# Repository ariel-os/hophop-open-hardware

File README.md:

hophop: Open Hardware
=====================

This repository will contains the design files
for hardware developed for hophop.

Items
-----

* [Grasshopper Nymph](./grasshopper-nymph/README.md)

  Status: Boards built and are being tested.

Branding
--------

These boards are developed as part of the Ariel OS project (as is the hophop stack),
will run Ariel OS based software from the start,
and may come with the Ariel OS logo.

License
-------

Data in this repository is licensed under the terms of [CERN-OHL-P-2.0](https://ohwr.org/cern_ohl_p_v2.pdf),
unless specified differently (when derived from third party content).

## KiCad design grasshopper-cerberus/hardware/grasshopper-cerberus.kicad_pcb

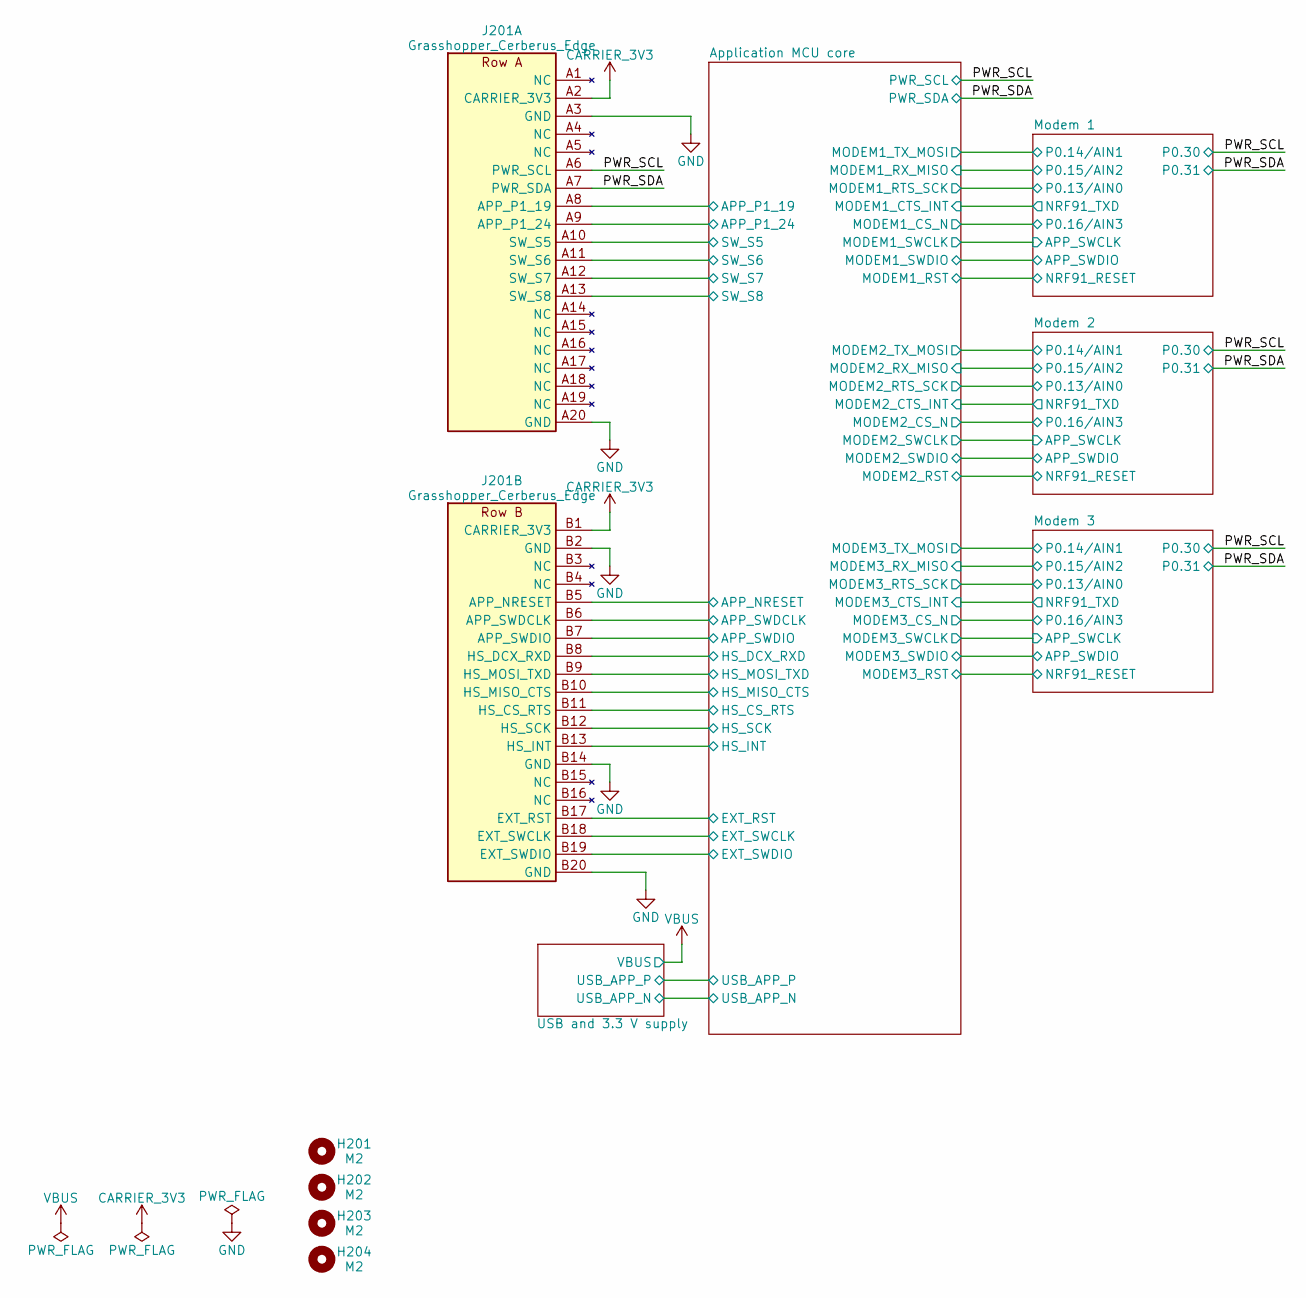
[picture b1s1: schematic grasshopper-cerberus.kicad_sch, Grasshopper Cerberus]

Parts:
H201, H202, H203, H204: M2; MountingHole_2.2mm_M2
J201: Grasshopper_Cerberus_Edge; Grasshopper_Cerberus_Edge_2x20_P2.54mm_Castellated_Row45.72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

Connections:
/Application MCU core/APP_NRESET: J201.B5 (APP_NRESET); also elsewhere on the board
/Application MCU core/APP_P1_19: J201.A8 (APP_P1_19); also elsewhere on the board
/Application MCU core/APP_P1_24: J201.A9 (APP_P1_24); also elsewhere on the board
/Application MCU core/APP_SWDCLK: J201.B6 (APP_SWDCLK); also elsewhere on the board
/Application MCU core/APP_SWDIO: J201.B7 (APP_SWDIO); also elsewhere on the board
/Application MCU core/EXT_RST: J201.B17 (EXT_RST); also elsewhere on the board
/Application MCU core/EXT_SWCLK: J201.B18 (EXT_SWCLK); also elsewhere on the board
/Application MCU core/EXT_SWDIO: J201.B19 (EXT_SWDIO); also elsewhere on the board
/Application MCU core/HS_CS_RTS: J201.B11 (HS_CS_RTS); also elsewhere on the board
/Application MCU core/HS_DCX_RXD: J201.B8 (HS_DCX_RXD); also elsewhere on the board
/Application MCU core/HS_INT: J201.B13 (HS_INT); also elsewhere on the board
/Application MCU core/HS_MISO_CTS: J201.B10 (HS_MISO_CTS); also elsewhere on the board
/Application MCU core/HS_MOSI_TXD: J201.B9 (HS_MOSI_TXD); also elsewhere on the board
/Application MCU core/HS_SCK: J201.B12 (HS_SCK); also elsewhere on the board
/Application MCU core/SW_S5: J201.A10 (SW_S5); also elsewhere on the board
/Application MCU core/SW_S6: J201.A11 (SW_S6); also elsewhere on the board
/Application MCU core/SW_S7: J201.A12 (SW_S7); also elsewhere on the board
/Application MCU core/SW_S8: J201.A13 (SW_S8); also elsewhere on the board
/PWR_SCL: J201.A6 (PWR_SCL); also elsewhere on the board
/PWR_SDA: J201.A7 (PWR_SDA); also elsewhere on the board
CARRIER_3V3: J201.A2 (CARRIER_3V3), J201.B1 (CARRIER_3V3); also elsewhere on the board
GND: J201.A3 (GND), J201.A20 (GND), J201.B2 (GND), J201.B14 (GND), J201.B20 (GND); also elsewhere on the board

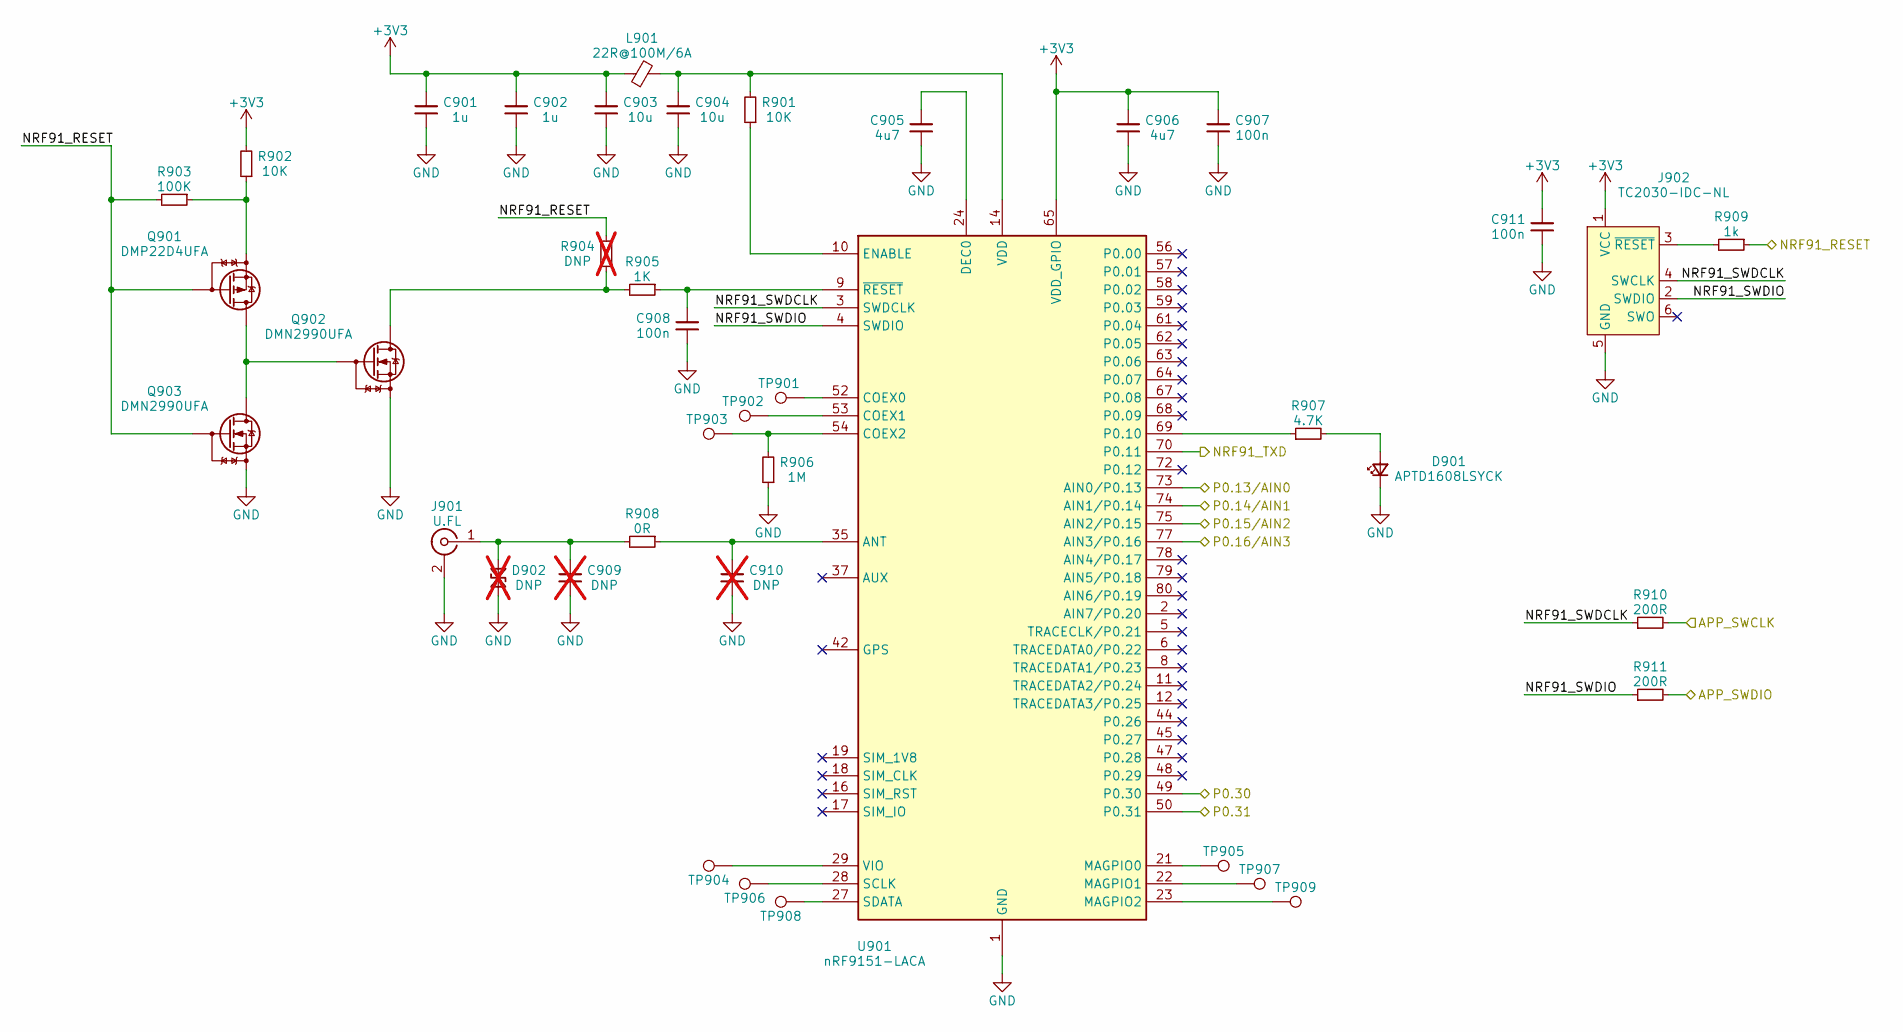
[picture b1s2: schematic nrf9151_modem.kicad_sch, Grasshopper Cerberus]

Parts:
C901, C902: 1u; C_0402_1005Metric; MPN GRM155R61A105KE15D
C903, C904: 10u; C_0603_1608Metric; MPN GRM188R61A106KE69D
C905, C906: 4u7; C_0402_1005Metric; MPN GRM155R61A475MEAAD
C907, C908: 100n; C_0402_1005Metric; MPN GRM155R71C104KA88D
C909, C910: DNP; C_0402_1005Metric; not fitted
C911: 100n; C_0402_1005Metric
D901: APTD1608LSYCK; LED_0603_1608Metric; MPN APTD1608LSYCK
D902: DNP; D_SOD-882; not fitted
J901: U.FL; U.FL_Hirose_U.FL-R-SMT-1_Vertical; MPN U.FL-R-SMT-1(10)
J902: TC2030-IDC-NL; Tag-Connect_TC2030-IDC-NL_2x03_P1.27mm_Vertical
L901: 22R@100M/6A; L_0805_2012Metric; MPN BLM21PG220SN1D
Q901: DMP22D4UFA; Diodes_X2-DFN0806-3_0.8x0.6mm_P0.35mm_GSD; MPN DMP22D4UFA-7B
Q902, Q903: DMN2990UFA; Diodes_X2-DFN0806-3_0.8x0.6mm_P0.35mm_GSD; MPN DMN2990UFA-7B
R901, R902: 10K; R_0402_1005Metric; MPN CRCW040210K0FKED
R903: 100K; R_0402_1005Metric; MPN CRCW0402100KFKED
R904: DNP; R_0402_1005Metric; MPN CRCW04020000Z0ED; not fitted
R905: 1K; R_0402_1005Metric; MPN CRCW04021K00FKED
R906: 1M; R_0402_1005Metric; MPN CRCW04021M00FKED
R907: 4.7K; R_0402_1005Metric; Tolerance 1%; MPN CRCW04024K70FKED
R908: 0R; R_0402_1005Metric; MPN CRCW04020000Z0ED
R909: 1k; R_0402_1005Metric
R910, R911: 200R; R_0402_1005Metric
TP901, TP902, TP903, TP904, TP905, TP906, TP907, TP908, TP909: TestPoint; TestPoint_Pad_D1.0mm_Compact
U901: nRF9151-LACA; Nordic_nRF9151-LAxx_LGA-80-33EP_12.1x11.1mm_P0.5mm; MPN nRF9151-LACA-R7

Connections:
+3V3: C901.2, C902.2, C903.2, C906.2, C907.2, C911.1, J902.1 (VCC), L901.1, R902.2, U901.65 (VDD_GPIO); also elsewhere on the board
/Application MCU core/MODEM1_CS_N: U901.77 (AIN3/P0.16); also elsewhere on the board
/Application MCU core/MODEM1_CTS_INT: U901.70 (P0.11); also elsewhere on the board
/Application MCU core/MODEM1_RTS_SCK: U901.73 (AIN0/P0.13); also elsewhere on the board
/Application MCU core/MODEM1_RX_MISO: U901.75 (AIN2/P0.15); also elsewhere on the board
/Application MCU core/MODEM1_SWCLK: R910.2; also elsewhere on the board
/Application MCU core/MODEM1_SWDIO: R911.2; also elsewhere on the board
/Application MCU core/MODEM1_TX_MOSI: U901.74 (AIN1/P0.14); also elsewhere on the board
/Modem 1/NRF91_RESET: Q901.G, Q903.G, R903.2, R904.1, R909.1; also elsewhere on the board
/Modem 1/NRF91_SWDCLK: J902.4 (SWCLK), R910.1, U901.3 (SWDCLK)
/Modem 1/NRF91_SWDIO: J902.2 (SWDIO), R911.1, U901.4 (SWDIO)
/PWR_SCL: U901.49 (P0.30); also elsewhere on the board
/PWR_SDA: U901.50 (P0.31); also elsewhere on the board
GND: C901.1, C902.1, C903.1, C904.1, C905.1, C906.1, C907.1, C908.1, C909.1, C910.1, C911.2, D901.1 (K), D902.2 (A2), J901.2 (Ext), J902.5 (GND), Q902.S, Q903.S, R906.1, U901.1 (GND), U901.7 (GND), U901.13 (GND), U901.15 (GND), U901.20 (GND), U901.25 (GND), U901.30 (GND), U901.34 (GND), U901.36 (GND), U901.38 (GND), U901.39 (GND), U901.40 (GND), U901.41 (GND), U901.43 (GND), U901.46 (GND), U901.51 (GND), U901.55 (GND), U901.60 (GND), U901.66 (GND), U901.71 (GND), U901.76 (GND), U901.105 (GND), U901.106 (GND), U901.107 (GND), U901.108 (GND), U901.109 (GND), U901.110 (GND), U901.111 (GND), U901.112 (GND), U901.113 (GND); also elsewhere on the board
unnamed: D901.2 (A), R907.2
unnamed: C909.2, D902.1 (A1), J901.1 (In), R908.2
unnamed: J902.3 (~RESET), R909.2
unnamed: Q901.D, Q902.G, Q903.D
unnamed: Q901.S, R902.1, R903.1
unnamed: Q902.D, R904.2, R905.2
unnamed: C910.2, R908.1, U901.35 (ANT)
unnamed: TP901.1 (1_1), U901.52 (COEX0)
unnamed: TP902.1 (1_1), U901.53 (COEX1)
unnamed: R906.2, TP903.1 (1_1), U901.54 (COEX2)
unnamed: C905.2, U901.24 (DEC0)
unnamed: R901.1, U901.10 (ENABLE)
unnamed: TP905.1 (1_1), U901.21 (MAGPIO0)
unnamed: TP907.1 (1_1), U901.22 (MAGPIO1)
unnamed: TP909.1 (1_1), U901.23 (MAGPIO2)
unnamed: R907.1, U901.69 (P0.10)
unnamed: TP906.1 (1_1), U901.28 (SCLK)
unnamed: TP908.1 (1_1), U901.27 (SDATA)
unnamed: C904.2, L901.2, R901.2, U901.14 (VDD)
unnamed: TP904.1 (1_1), U901.29 (VIO)
unnamed: C908.2, R905.1, U901.9 (~RESET)

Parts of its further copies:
C1001, C1002, C1101, C1102: 1u; C_0402_1005Metric; MPN GRM155R61A105KE15D
C1003, C1004, C1103, C1104: 10u; C_0603_1608Metric; MPN GRM188R61A106KE69D
C1005, C1006, C1105, C1106: 4u7; C_0402_1005Metric; MPN GRM155R61A475MEAAD
C1007, C1008, C1107, C1108: 100n; C_0402_1005Metric; MPN GRM155R71C104KA88D
C1009, C1010, C1109, C1110: DNP; C_0402_1005Metric; not fitted
C1011, C1111: 100n; C_0402_1005Metric
D1001, D1101: APTD1608LSYCK; LED_0603_1608Metric; MPN APTD1608LSYCK
D1002, D1102: DNP; D_SOD-882; not fitted
J1001, J1101: U.FL; U.FL_Hirose_U.FL-R-SMT-1_Vertical; MPN U.FL-R-SMT-1(10)
J1002, J1102: TC2030-IDC-NL; Tag-Connect_TC2030-IDC-NL_2x03_P1.27mm_Vertical
L1001, L1101: 22R@100M/6A; L_0805_2012Metric; MPN BLM21PG220SN1D
Q1001, Q1101: DMP22D4UFA; Diodes_X2-DFN0806-3_0.8x0.6mm_P0.35mm_GSD; MPN DMP22D4UFA-7B
Q1002, Q1003, Q1102, Q1103: DMN2990UFA; Diodes_X2-DFN0806-3_0.8x0.6mm_P0.35mm_GSD; MPN DMN2990UFA-7B
R1001, R1002, R1101, R1102: 10K; R_0402_1005Metric; MPN CRCW040210K0FKED
R1003, R1103: 100K; R_0402_1005Metric; MPN CRCW0402100KFKED
R1004, R1104: DNP; R_0402_1005Metric; MPN CRCW04020000Z0ED; not fitted
R1005, R1105: 1K; R_0402_1005Metric; MPN CRCW04021K00FKED
R1006, R1106: 1M; R_0402_1005Metric; MPN CRCW04021M00FKED
R1007, R1107: 4.7K; R_0402_1005Metric; Tolerance 1%; MPN CRCW04024K70FKED
R1008, R1108: 0R; R_0402_1005Metric; MPN CRCW04020000Z0ED
R1009, R1109: 1k; R_0402_1005Metric
R1010, R1011, R1110, R1111: 200R; R_0402_1005Metric
TP1001, TP1002, TP1003, TP1004, TP1005, TP1006, TP1007, TP1008, TP1009, TP1101, TP1102, TP1103, TP1104, TP1105, TP1106, TP1107, TP1108, TP1109: TestPoint; TestPoint_Pad_D1.0mm_Compact
U1001, U1101: nRF9151-LACA; Nordic_nRF9151-LAxx_LGA-80-33EP_12.1x11.1mm_P0.5mm; MPN nRF9151-LACA-R7

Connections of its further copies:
+3V3: C1001.2, C1002.2, C1003.2, C1006.2, C1007.2, C1011.1, C1101.2, C1102.2, C1103.2, C1106.2, C1107.2, C1111.1, J1002.1 (VCC), J1102.1 (VCC), L1001.1, L1101.1, R1002.2, R1102.2, U1001.65 (VDD_GPIO), U1101.65 (VDD_GPIO); also elsewhere on the board
/Application MCU core/MODEM2_CS_N: U1001.77 (AIN3/P0.16); also elsewhere on the board
/Application MCU core/MODEM2_CTS_INT: U1001.70 (P0.11); also elsewhere on the board
/Application MCU core/MODEM2_RTS_SCK: U1001.73 (AIN0/P0.13); also elsewhere on the board
/Application MCU core/MODEM2_RX_MISO: U1001.75 (AIN2/P0.15); also elsewhere on the board
/Application MCU core/MODEM2_SWCLK: R1010.2; also elsewhere on the board
/Application MCU core/MODEM2_SWDIO: R1011.2; also elsewhere on the board
/Application MCU core/MODEM2_TX_MOSI: U1001.74 (AIN1/P0.14); also elsewhere on the board
/Application MCU core/MODEM3_CS_N: U1101.77 (AIN3/P0.16); also elsewhere on the board
/Application MCU core/MODEM3_CTS_INT: U1101.70 (P0.11); also elsewhere on the board
/Application MCU core/MODEM3_RTS_SCK: U1101.73 (AIN0/P0.13); also elsewhere on the board
/Application MCU core/MODEM3_RX_MISO: U1101.75 (AIN2/P0.15); also elsewhere on the board
/Application MCU core/MODEM3_SWCLK: R1110.2; also elsewhere on the board
/Application MCU core/MODEM3_SWDIO: R1111.2; also elsewhere on the board
/Application MCU core/MODEM3_TX_MOSI: U1101.74 (AIN1/P0.14); also elsewhere on the board
/Modem 2/NRF91_RESET: Q1001.G, Q1003.G, R1003.2, R1004.1, R1009.1; also elsewhere on the board
/Modem 2/NRF91_SWDCLK: J1002.4 (SWCLK), R1010.1, U1001.3 (SWDCLK)
/Modem 2/NRF91_SWDIO: J1002.2 (SWDIO), R1011.1, U1001.4 (SWDIO)
/Modem 3/NRF91_RESET: Q1101.G, Q1103.G, R1103.2, R1104.1, R1109.1; also elsewhere on the board
/Modem 3/NRF91_SWDCLK: J1102.4 (SWCLK), R1110.1, U1101.3 (SWDCLK)
/Modem 3/NRF91_SWDIO: J1102.2 (SWDIO), R1111.1, U1101.4 (SWDIO)
/PWR_SCL: U1001.49 (P0.30), U1101.49 (P0.30); also elsewhere on the board
/PWR_SDA: U1001.50 (P0.31), U1101.50 (P0.31); also elsewhere on the board
GND: C1001.1, C1002.1, C1003.1, C1004.1, C1005.1, C1006.1, C1007.1, C1008.1, C1009.1, C1010.1, C1011.2, C1101.1, C1102.1, C1103.1, C1104.1, C1105.1, C1106.1, C1107.1, C1108.1, C1109.1, C1110.1, C1111.2, D1001.1 (K), D1002.2 (A2), D1101.1 (K), D1102.2 (A2), J1001.2 (Ext), J1002.5 (GND), J1101.2 (Ext), J1102.5 (GND), Q1002.S, Q1003.S, Q1102.S, Q1103.S, R1006.1, R1106.1, U1001.1 (GND), U1001.7 (GND), U1001.13 (GND), U1001.15 (GND), U1001.20 (GND), U1001.25 (GND), U1001.30 (GND), U1001.34 (GND), U1001.36 (GND), U1001.38 (GND), U1001.39 (GND), U1001.40 (GND), U1001.41 (GND), U1001.43 (GND), U1001.46 (GND), U1001.51 (GND), U1001.55 (GND), U1001.60 (GND), U1001.66 (GND), U1001.71 (GND), U1001.76 (GND), U1001.105 (GND), U1001.106 (GND), U1001.107 (GND), U1001.108 (GND), U1001.109 (GND), U1001.110 (GND), U1001.111 (GND), U1001.112 (GND), U1001.113 (GND), U1101.1 (GND), U1101.7 (GND), U1101.13 (GND), U1101.15 (GND), U1101.20 (GND), U1101.25 (GND), U1101.30 (GND), U1101.34 (GND), U1101.36 (GND), U1101.38 (GND), U1101.39 (GND), U1101.40 (GND), U1101.41 (GND), U1101.43 (GND), U1101.46 (GND), U1101.51 (GND), U1101.55 (GND), U1101.60 (GND), U1101.66 (GND), U1101.71 (GND), U1101.76 (GND), U1101.105 (GND), U1101.106 (GND), U1101.107 (GND), U1101.108 (GND), U1101.109 (GND), U1101.110 (GND), U1101.111 (GND), U1101.112 (GND), U1101.113 (GND); also elsewhere on the board
unnamed: D1001.2 (A), R1007.2
unnamed: C1009.2, D1002.1 (A1), J1001.1 (In), R1008.2
unnamed: D1101.2 (A), R1107.2
unnamed: C1109.2, D1102.1 (A1), J1101.1 (In), R1108.2
unnamed: J1002.3 (~RESET), R1009.2
unnamed: J1102.3 (~RESET), R1109.2
unnamed: Q1001.D, Q1002.G, Q1003.D
unnamed: Q1001.S, R1002.1, R1003.1
unnamed: Q1002.D, R1004.2, R1005.2
unnamed: Q1101.D, Q1102.G, Q1103.D
unnamed: Q1101.S, R1102.1, R1103.1
unnamed: Q1102.D, R1104.2, R1105.2
unnamed: C1010.2, R1008.1, U1001.35 (ANT)
unnamed: TP1001.1 (1_1), U1001.52 (COEX0)
unnamed: TP1002.1 (1_1), U1001.53 (COEX1)
unnamed: R1006.2, TP1003.1 (1_1), U1001.54 (COEX2)
unnamed: C1005.2, U1001.24 (DEC0)
unnamed: R1001.1, U1001.10 (ENABLE)
unnamed: TP1005.1 (1_1), U1001.21 (MAGPIO0)
unnamed: TP1007.1 (1_1), U1001.22 (MAGPIO1)
unnamed: TP1009.1 (1_1), U1001.23 (MAGPIO2)
unnamed: R1007.1, U1001.69 (P0.10)
unnamed: TP1006.1 (1_1), U1001.28 (SCLK)
unnamed: TP1008.1 (1_1), U1001.27 (SDATA)
unnamed: C1004.2, L1001.2, R1001.2, U1001.14 (VDD)
unnamed: TP1004.1 (1_1), U1001.29 (VIO)
unnamed: C1008.2, R1005.1, U1001.9 (~RESET)
unnamed: C1110.2, R1108.1, U1101.35 (ANT)
unnamed: TP1101.1 (1_1), U1101.52 (COEX0)
unnamed: TP1102.1 (1_1), U1101.53 (COEX1)
unnamed: R1106.2, TP1103.1 (1_1), U1101.54 (COEX2)
unnamed: C1105.2, U1101.24 (DEC0)
unnamed: R1101.1, U1101.10 (ENABLE)
unnamed: TP1105.1 (1_1), U1101.21 (MAGPIO0)
unnamed: TP1107.1 (1_1), U1101.22 (MAGPIO1)
unnamed: TP1109.1 (1_1), U1101.23 (MAGPIO2)
unnamed: R1107.1, U1101.69 (P0.10)
unnamed: TP1106.1 (1_1), U1101.28 (SCLK)
unnamed: TP1108.1 (1_1), U1101.27 (SDATA)
unnamed: C1104.2, L1101.2, R1101.2, U1101.14 (VDD)
unnamed: TP1104.1 (1_1), U1101.29 (VIO)
unnamed: C1108.2, R1105.1, U1101.9 (~RESET)

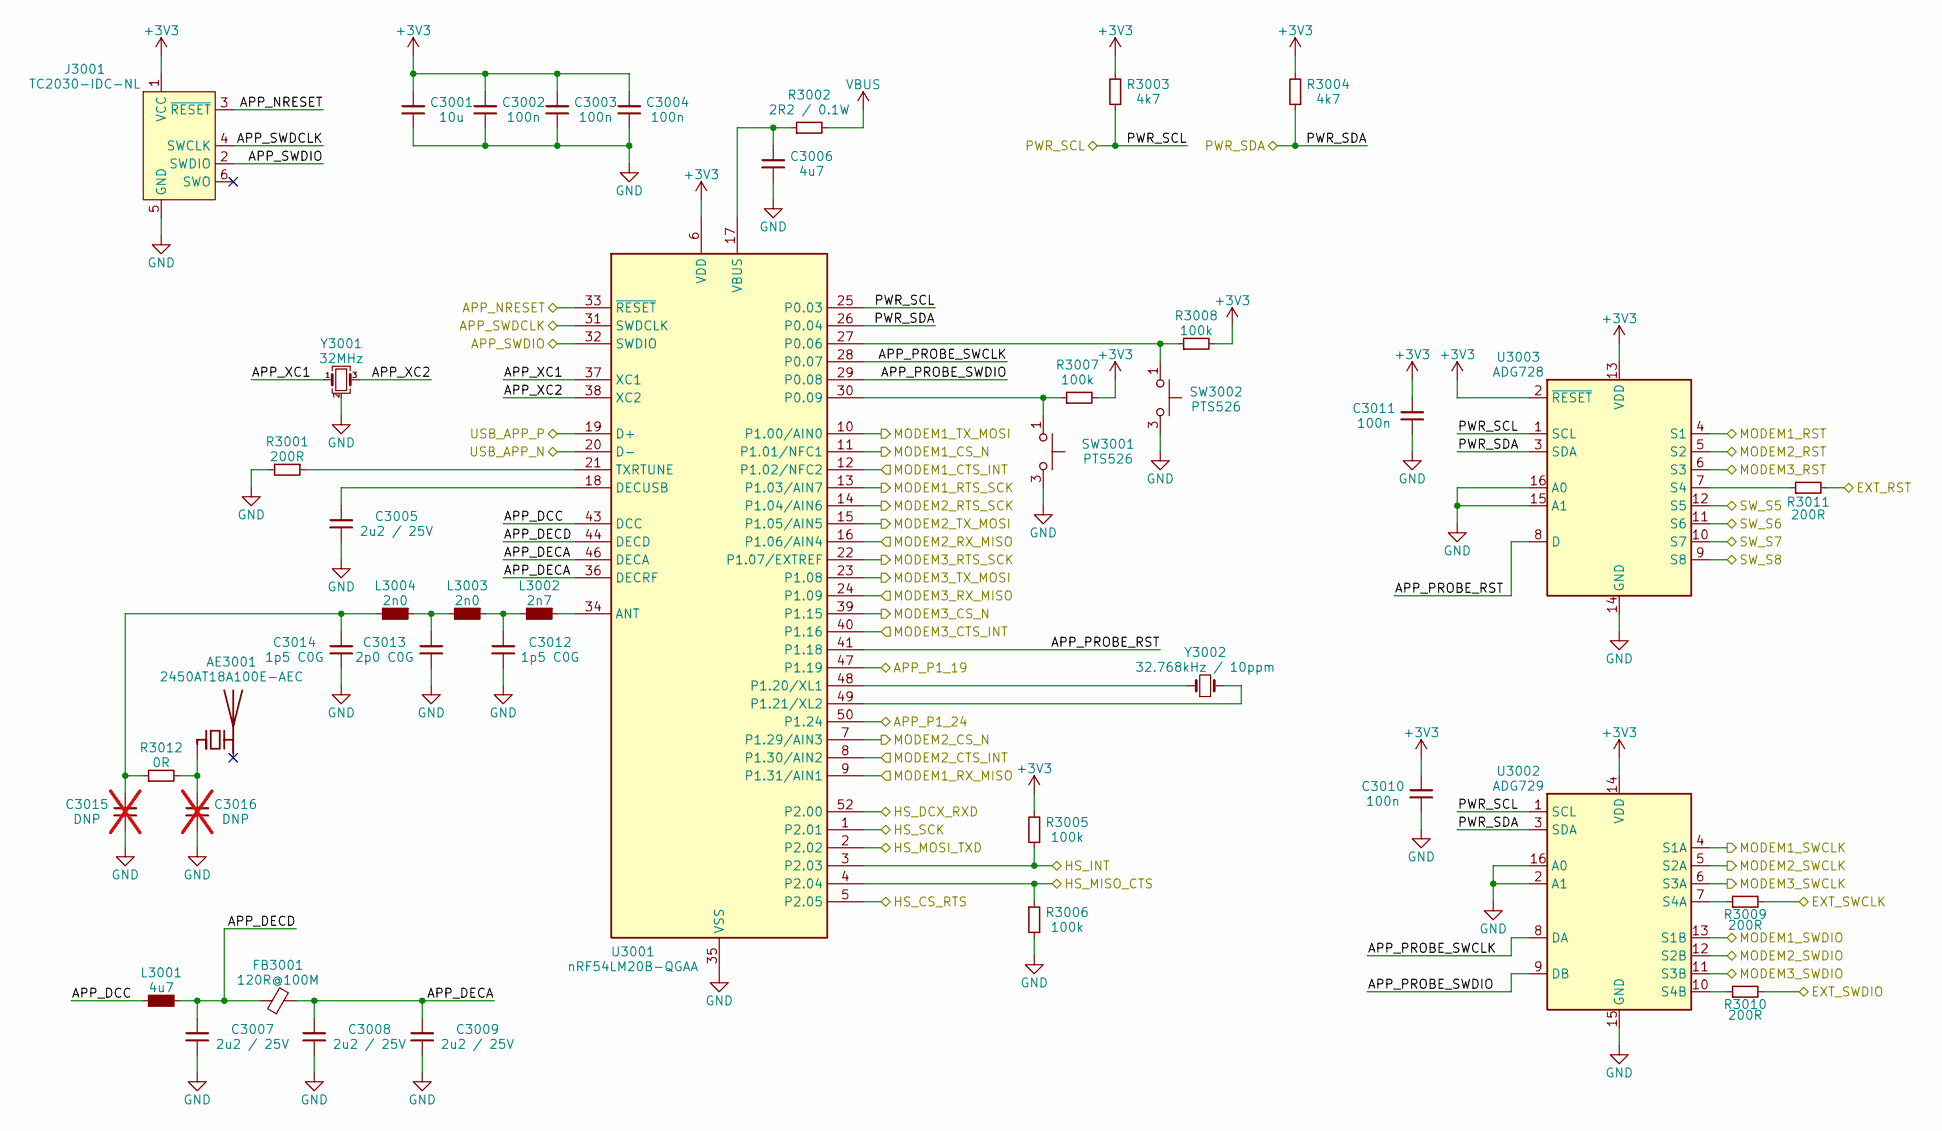
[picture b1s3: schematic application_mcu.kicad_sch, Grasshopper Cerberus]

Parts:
AE3001: 2450AT18A100E-AEC; Johanson_2450AT18x100
C3001: 10u; C_0603_1608Metric
C3002, C3003, C3004, C3010, C3011: 100n; C_0402_1005Metric
C3005, C3007, C3008, C3009: 2u2 / 25V; C_0402_1005Metric
C3006: 4u7; C_0402_1005Metric
C3012, C3014: 1p5 C0G; C_0201_0603Metric_Nordic_nRF54LM20_RF
C3013: 2p0 C0G; C_0201_0603Metric_Nordic_nRF54LM20_RF
C3015, C3016: DNP; C_0201_0603Metric_Nordic_nRF54LM20_RF; not fitted
FB3001: 120R@100M; L_Murata_BLM18_1608Metric
J3001: TC2030-IDC-NL; Tag-Connect_TC2030-IDC-NL_2x03_P1.27mm_Vertical
L3001: 4u7; L_TDK_MLZ1608
L3002: 2n7; L_0201_0603Metric_Nordic_nRF54LM20_RF
L3003, L3004: 2n0; L_0201_0603Metric_Nordic_nRF54LM20_RF
R3001, R3009, R3010, R3011: 200R; R_0402_1005Metric
R3002: 2R2 / 0.1W; R_0603_1608Metric
R3003, R3004: 4k7; R_0402_1005Metric
R3005, R3006, R3007, R3008: 100k; R_0402_1005Metric
R3012: 0R; R_0402_1005Metric
SW3001, SW3002: PTS526; SW_SPST_CK_PTS526SM15SMTR2
U3001: nRF54LM20B-QGAA; VQFN-52-1EP_6x6mm_P0.4mm_EP4.7x4.7mm_ThermalVias_Nordic_nRF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
U3002: ADG729; TSSOP-16_4.4x5mm_P0.65mm
U3003: ADG728; TSSOP-16_4.4x5mm_P0.65mm
Y3001: 32MHz; Abracon_ABM11W_2.0x1.6mm
Y3002: 32.768kHz / 10ppm; Abracon_ABS06_2.0x1.2mm

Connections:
+3V3: C3001.1, C3002.1, C3003.1, C3004.1, C3010.1, C3011.1, J3001.1 (VCC), R3003.2, R3004.2, R3005.2, R3007.2, R3008.2, U3001.6 (VDD), U3001.42 (VDD), U3001.51 (VDD), U3002.14 (VDD), U3003.2 (~RESET), U3003.13 (VDD); also elsewhere on the board
/Application MCU core/APP_DCC: L3001.1, U3001.43 (DCC)
/Application MCU core/APP_DECA: C3008.1, C3009.1, FB3001.2, U3001.36 (DECRF), U3001.46 (DECA)
/Application MCU core/APP_DECD: C3007.1, FB3001.1, L3001.2, U3001.44 (DECD)
/Application MCU core/APP_NRESET: J3001.3 (~RESET), U3001.33 (~RESET); also elsewhere on the board
/Application MCU core/APP_P1_19: U3001.47 (P1.19); also elsewhere on the board
/Application MCU core/APP_P1_24: U3001.50 (P1.24); also elsewhere on the board
/Application MCU core/APP_PROBE_RST: U3001.41 (P1.18), U3003.8 (D)
/Application MCU core/APP_PROBE_SWCLK: U3001.28 (P0.07), U3002.8 (DA)
/Application MCU core/APP_PROBE_SWDIO: U3001.29 (P0.08), U3002.9 (DB)
/Application MCU core/APP_SWDCLK: J3001.4 (SWCLK), U3001.31 (SWDCLK); also elsewhere on the board
/Application MCU core/APP_SWDIO: J3001.2 (SWDIO), U3001.32 (SWDIO); also elsewhere on the board
/Application MCU core/APP_XC1: U3001.37 (XC1), Y3001.1
/Application MCU core/APP_XC2: U3001.38 (XC2), Y3001.3
/Application MCU core/EXT_RST: R3011.2; also elsewhere on the board
/Application MCU core/EXT_SWCLK: R3009.2; also elsewhere on the board
/Application MCU core/EXT_SWDIO: R3010.2; also elsewhere on the board
/Application MCU core/HS_CS_RTS: U3001.5 (P2.05); also elsewhere on the board
/Application MCU core/HS_DCX_RXD: U3001.52 (P2.00); also elsewhere on the board
/Application MCU core/HS_INT: R3005.1, U3001.3 (P2.03); also elsewhere on the board
/Application MCU core/HS_MISO_CTS: R3006.1, U3001.4 (P2.04); also elsewhere on the board
/Application MCU core/HS_MOSI_TXD: U3001.2 (P2.02); also elsewhere on the board
/Application MCU core/HS_SCK: U3001.1 (P2.01); also elsewhere on the board
/Application MCU core/MODEM1_CS_N: U3001.11 (P1.01/NFC1); also elsewhere on the board
/Application MCU core/MODEM1_CTS_INT: U3001.12 (P1.02/NFC2); also elsewhere on the board
/Application MCU core/MODEM1_RTS_SCK: U3001.13 (P1.03/AIN7); also elsewhere on the board
/Application MCU core/MODEM1_RX_MISO: U3001.9 (P1.31/AIN1); also elsewhere on the board
/Application MCU core/MODEM1_SWCLK: U3002.4 (S1A); also elsewhere on the board
/Application MCU core/MODEM1_SWDIO: U3002.13 (S1B); also elsewhere on the board
/Application MCU core/MODEM1_TX_MOSI: U3001.10 (P1.00/AIN0); also elsewhere on the board
/Application MCU core/MODEM2_CS_N: U3001.7 (P1.29/AIN3); also elsewhere on the board
/Application MCU core/MODEM2_CTS_INT: U3001.8 (P1.30/AIN2); also elsewhere on the board
/Application MCU core/MODEM2_RTS_SCK: U3001.14 (P1.04/AIN6); also elsewhere on the board
/Application MCU core/MODEM2_RX_MISO: U3001.16 (P1.06/AIN4); also elsewhere on the board
/Application MCU core/MODEM2_SWCLK: U3002.5 (S2A); also elsewhere on the board
/Application MCU core/MODEM2_SWDIO: U3002.12 (S2B); also elsewhere on the board
/Application MCU core/MODEM2_TX_MOSI: U3001.15 (P1.05/AIN5); also elsewhere on the board
/Application MCU core/MODEM3_CS_N: U3001.39 (P1.15); also elsewhere on the board
/Application MCU core/MODEM3_CTS_INT: U3001.40 (P1.16); also elsewhere on the board
/Application MCU core/MODEM3_RTS_SCK: U3001.22 (P1.07/EXTREF); also elsewhere on the board
/Application MCU core/MODEM3_RX_MISO: U3001.24 (P1.09); also elsewhere on the board
/Application MCU core/MODEM3_SWCLK: U3002.6 (S3A); also elsewhere on the board
/Application MCU core/MODEM3_SWDIO: U3002.11 (S3B); also elsewhere on the board
/Application MCU core/MODEM3_TX_MOSI: U3001.23 (P1.08); also elsewhere on the board
/Application MCU core/SW_S5: U3003.12 (S5); also elsewhere on the board
/Application MCU core/SW_S6: U3003.11 (S6); also elsewhere on the board
/Application MCU core/SW_S7: U3003.10 (S7); also elsewhere on the board
/Application MCU core/SW_S8: U3003.9 (S8); also elsewhere on the board
/Application MCU core/USB_APP_N: U3001.20 (D-); also elsewhere on the board
/Application MCU core/USB_APP_P: U3001.19 (D+); also elsewhere on the board
/Modem 1/NRF91_RESET: U3003.4 (S1); also elsewhere on the board
/Modem 2/NRF91_RESET: U3003.5 (S2); also elsewhere on the board
/Modem 3/NRF91_RESET: U3003.6 (S3); also elsewhere on the board
/PWR_SCL: R3003.1, U3001.25 (P0.03), U3002.1 (SCL), U3003.1 (SCL); also elsewhere on the board
/PWR_SDA: R3004.1, U3001.26 (P0.04), U3002.3 (SDA), U3003.3 (SDA); also elsewhere on the board
GND: C3001.2, C3002.2, C3003.2, C3004.2, C3005.2, C3006.2, C3007.2, C3008.2, C3009.2, C3010.2, C3011.2, C3012.2, C3013.2, C3014.2, C3015.2, C3016.2, J3001.5 (GND), R3001.2, R3006.2, SW3001.3 (2), SW3001.4 (2), SW3002.3 (2), SW3002.4 (2), U3001.35 (VSS), U3001.45 (VSS), U3001.53 (VSS), U3002.2 (A1), U3002.15 (GND), U3002.16 (A0), U3003.14 (GND), U3003.15 (A1), U3003.16 (A0), Y3001.2 (G), Y3001.4 (G); also elsewhere on the board
unnamed: AE3001.1 (FEED_1), C3016.1, R3012.2
unnamed: C3012.1, L3002.2, L3003.1
unnamed: C3013.1, L3003.2, L3004.1
unnamed: C3014.1, C3015.1, L3004.2, R3012.1
unnamed: L3002.1, U3001.34 (ANT)
unnamed: C3005.1, U3001.18 (DECUSB)
unnamed: R3008.1, SW3002.1, SW3002.2 (1), U3001.27 (P0.06)
unnamed: R3007.1, SW3001.1, SW3001.2 (1), U3001.30 (P0.09)
unnamed: U3001.48 (P1.20/XL1), Y3002.1
unnamed: U3001.49 (P1.21/XL2), Y3002.2
unnamed: R3001.1, U3001.21 (TXRTUNE)
unnamed: C3006.1, R3002.1, U3001.17 (VBUS)
unnamed: R3009.1, U3002.7 (S4A)
unnamed: R3010.1, U3002.10 (S4B)
unnamed: R3011.1, U3003.7 (S4)
VBUS: R3002.2; also elsewhere on the board

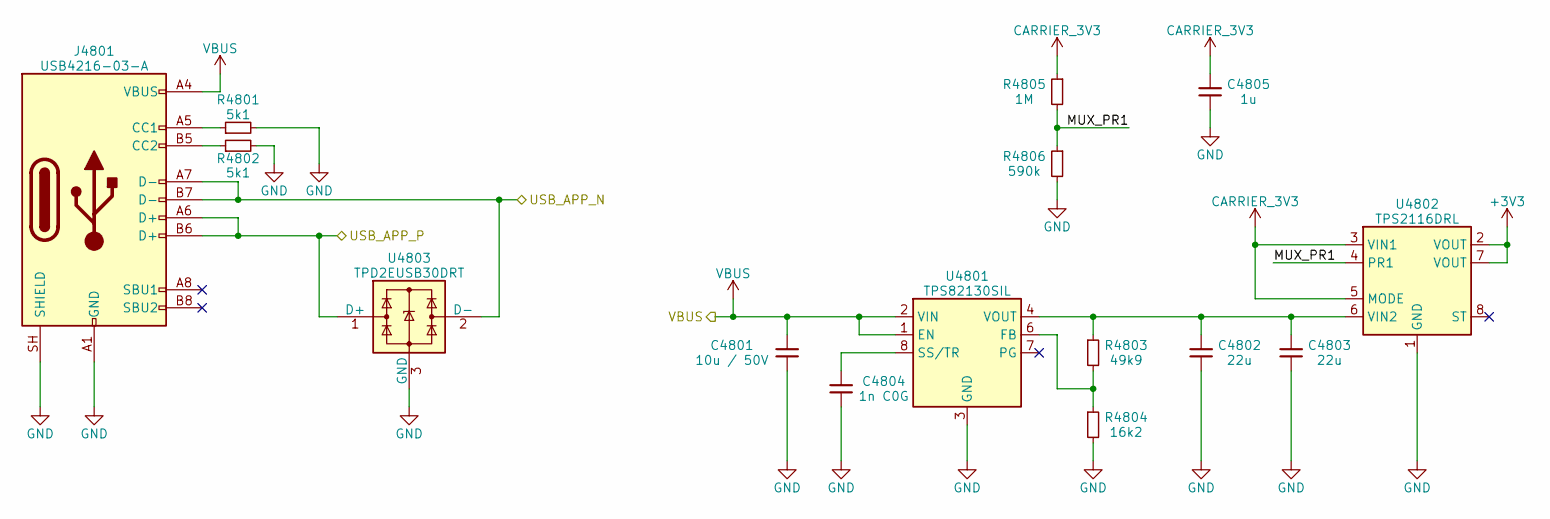
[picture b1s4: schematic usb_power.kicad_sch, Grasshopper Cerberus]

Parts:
C4801: 10u / 50V; C_1210_3225Metric
C4802, C4803: 22u; C_0603_1608Metric
C4804: 1n C0G; C_0402_1005Metric
C4805: 1u; C_0402_1005Metric
J4801: USB4216-03-A; USB_C_Receptacle_GCT_USB4216-03-A
R4801, R4802: 5k1; R_0402_1005Metric
R4803: 49k9; R_0402_1005Metric
R4804: 16k2; R_0402_1005Metric
R4805: 1M; R_0402_1005Metric
R4806: 590k; R_0402_1005Metric
U4801: TPS82130SIL; Texas_SIL0008D_MicroSiP-8-1EP_2.8x3mm_P0.65mm_EP1.1x1.9mm
U4802: TPS2116DRL; Texas_DRL0008A_SOT-583-8
U4803: TPD2EUSB30DRT; Texas_DRT-3

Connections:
+3V3: U4802.2 (VOUT), U4802.7 (VOUT); also elsewhere on the board
/Application MCU core/USB_APP_N: J4801.A7 (D-), J4801.B7 (D-), U4803.2 (D-); also elsewhere on the board
/Application MCU core/USB_APP_P: J4801.A6 (D+), J4801.B6 (D+), U4803.1 (D+); also elsewhere on the board
/USB and 3.3 V supply/MUX_PR1: R4805.2, R4806.1, U4802.4 (PR1)
CARRIER_3V3: C4805.1, R4805.1, U4802.3 (VIN1), U4802.5 (MODE); also elsewhere on the board
GND: C4801.2, C4802.2, C4803.2, C4804.2, C4805.2, J4801.A1 (GND), J4801.A12 (GND), J4801.B1 (GND), J4801.B12 (GND), J4801.SH (SHIELD), R4801.2, R4802.2, R4804.2, R4806.2, U4801.3 (GND), U4802.1 (GND), U4803.3 (GND); also elsewhere on the board
unnamed: J4801.A5 (CC1), R4801.1
unnamed: J4801.B5 (CC2), R4802.1
unnamed: R4803.2, R4804.1, U4801.6 (FB)
unnamed: C4804.1, U4801.8 (SS/TR)
unnamed: C4802.1, C4803.1, R4803.1, U4801.4 (VOUT), U4801.5 (VOUT), U4802.6 (VIN2)
VBUS: C4801.1, J4801.A4 (VBUS), J4801.A9 (VBUS), J4801.B4 (VBUS), J4801.B9 (VBUS), U4801.1 (EN), U4801.2 (VIN); also elsewhere on the board

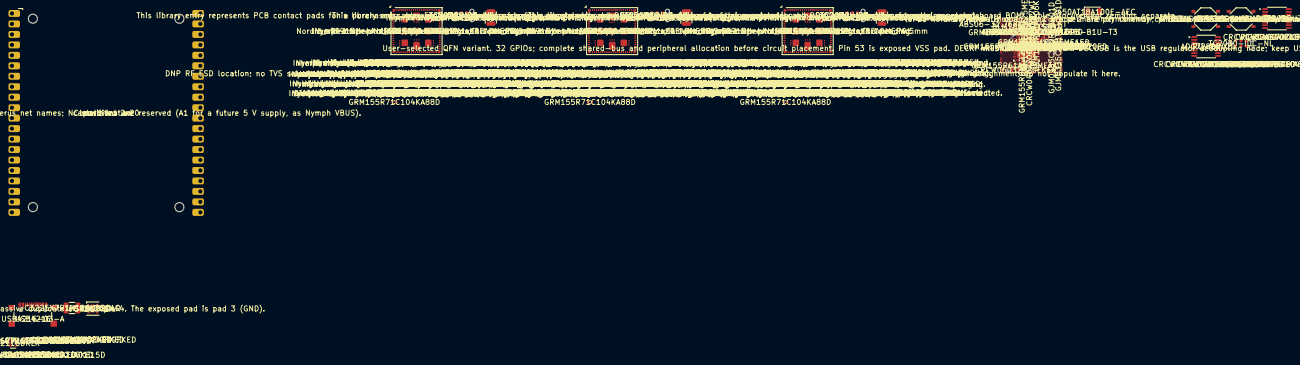
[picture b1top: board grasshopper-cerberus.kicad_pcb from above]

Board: 4 copper layers, 182 parts (0 on the bottom side), 148 nets.
